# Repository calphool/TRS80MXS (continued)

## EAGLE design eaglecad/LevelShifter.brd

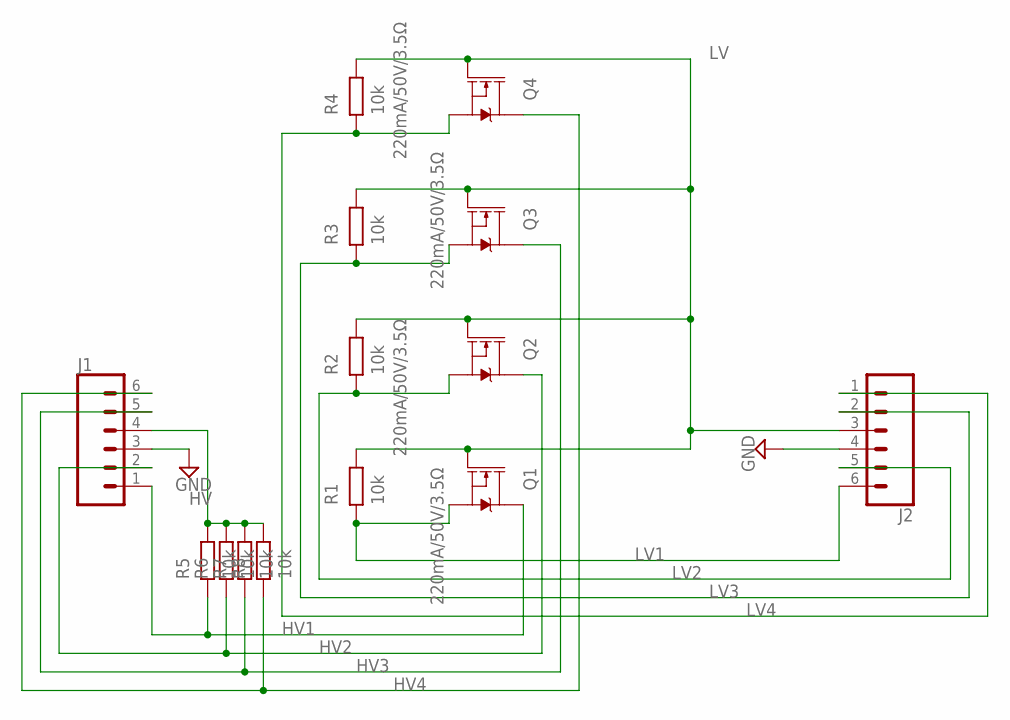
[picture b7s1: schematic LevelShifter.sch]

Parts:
J1, J2: CONN_06NO_SILK_NO_POP; 1X06_NO_SILK
Q1, Q2, Q3, Q4: 220mA/50V/3.5Ω; SOT23-3
R1, R2, R3, R4, R5, R6, R7, R8: 10k; RESC1608X60

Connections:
GND: J1.3, J2.4
HV: J1.4, R5.2, R6.2, R7.2, R8.2
HV1: J1.1, Q1.3 (D), R5.1
HV2: J1.2, Q2.3 (D), R6.1
HV3: J1.5, Q3.3 (D), R7.1
HV4: J1.6, Q4.3 (D), R8.1
LV: J2.3, Q1.1 (G), Q2.1 (G), Q3.1 (G), Q4.1 (G), R1.2, R2.2, R3.2, R4.2
LV1: J2.6, Q1.2 (S), R1.1
LV2: J2.5, Q2.2 (S), R2.1
LV3: J2.2, Q3.2 (S), R3.1
LV4: J2.1, Q4.2 (S), R4.1

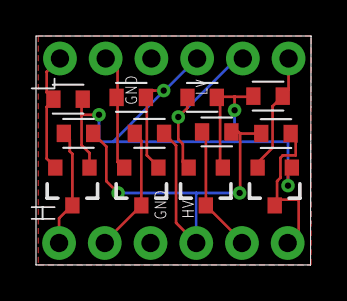
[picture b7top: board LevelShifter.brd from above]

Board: 2 copper layers, 15.3 x 12.7 mm, 14 parts (0 on the bottom side), 11 nets.

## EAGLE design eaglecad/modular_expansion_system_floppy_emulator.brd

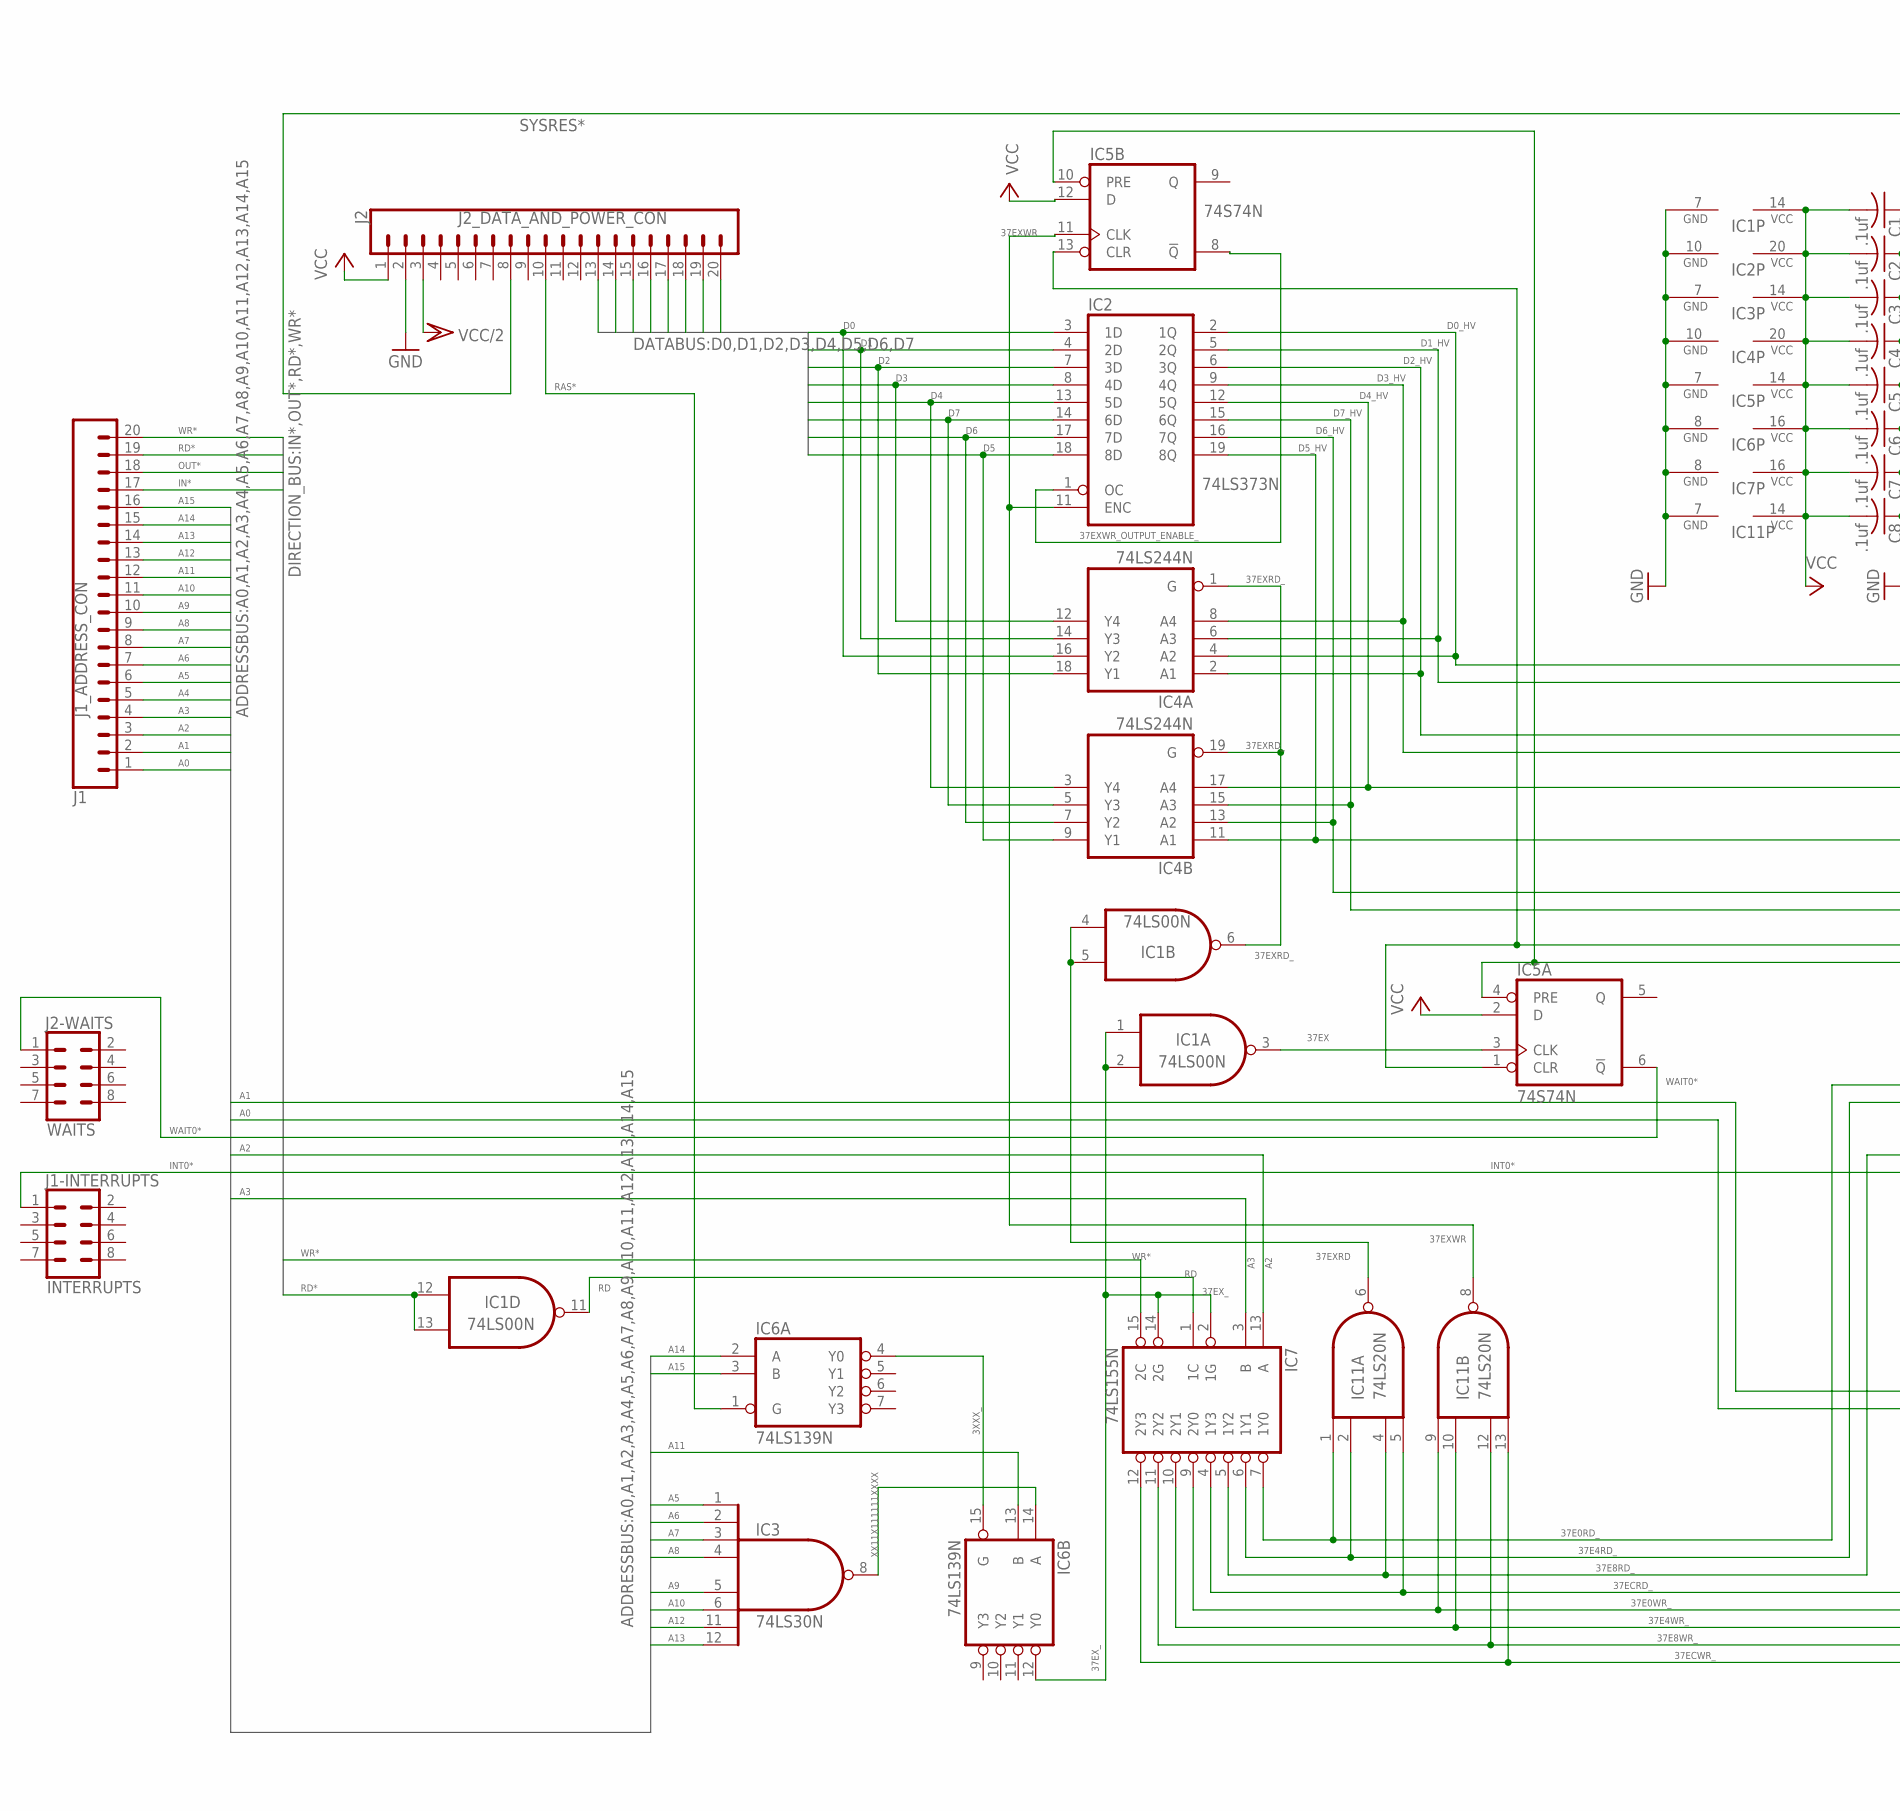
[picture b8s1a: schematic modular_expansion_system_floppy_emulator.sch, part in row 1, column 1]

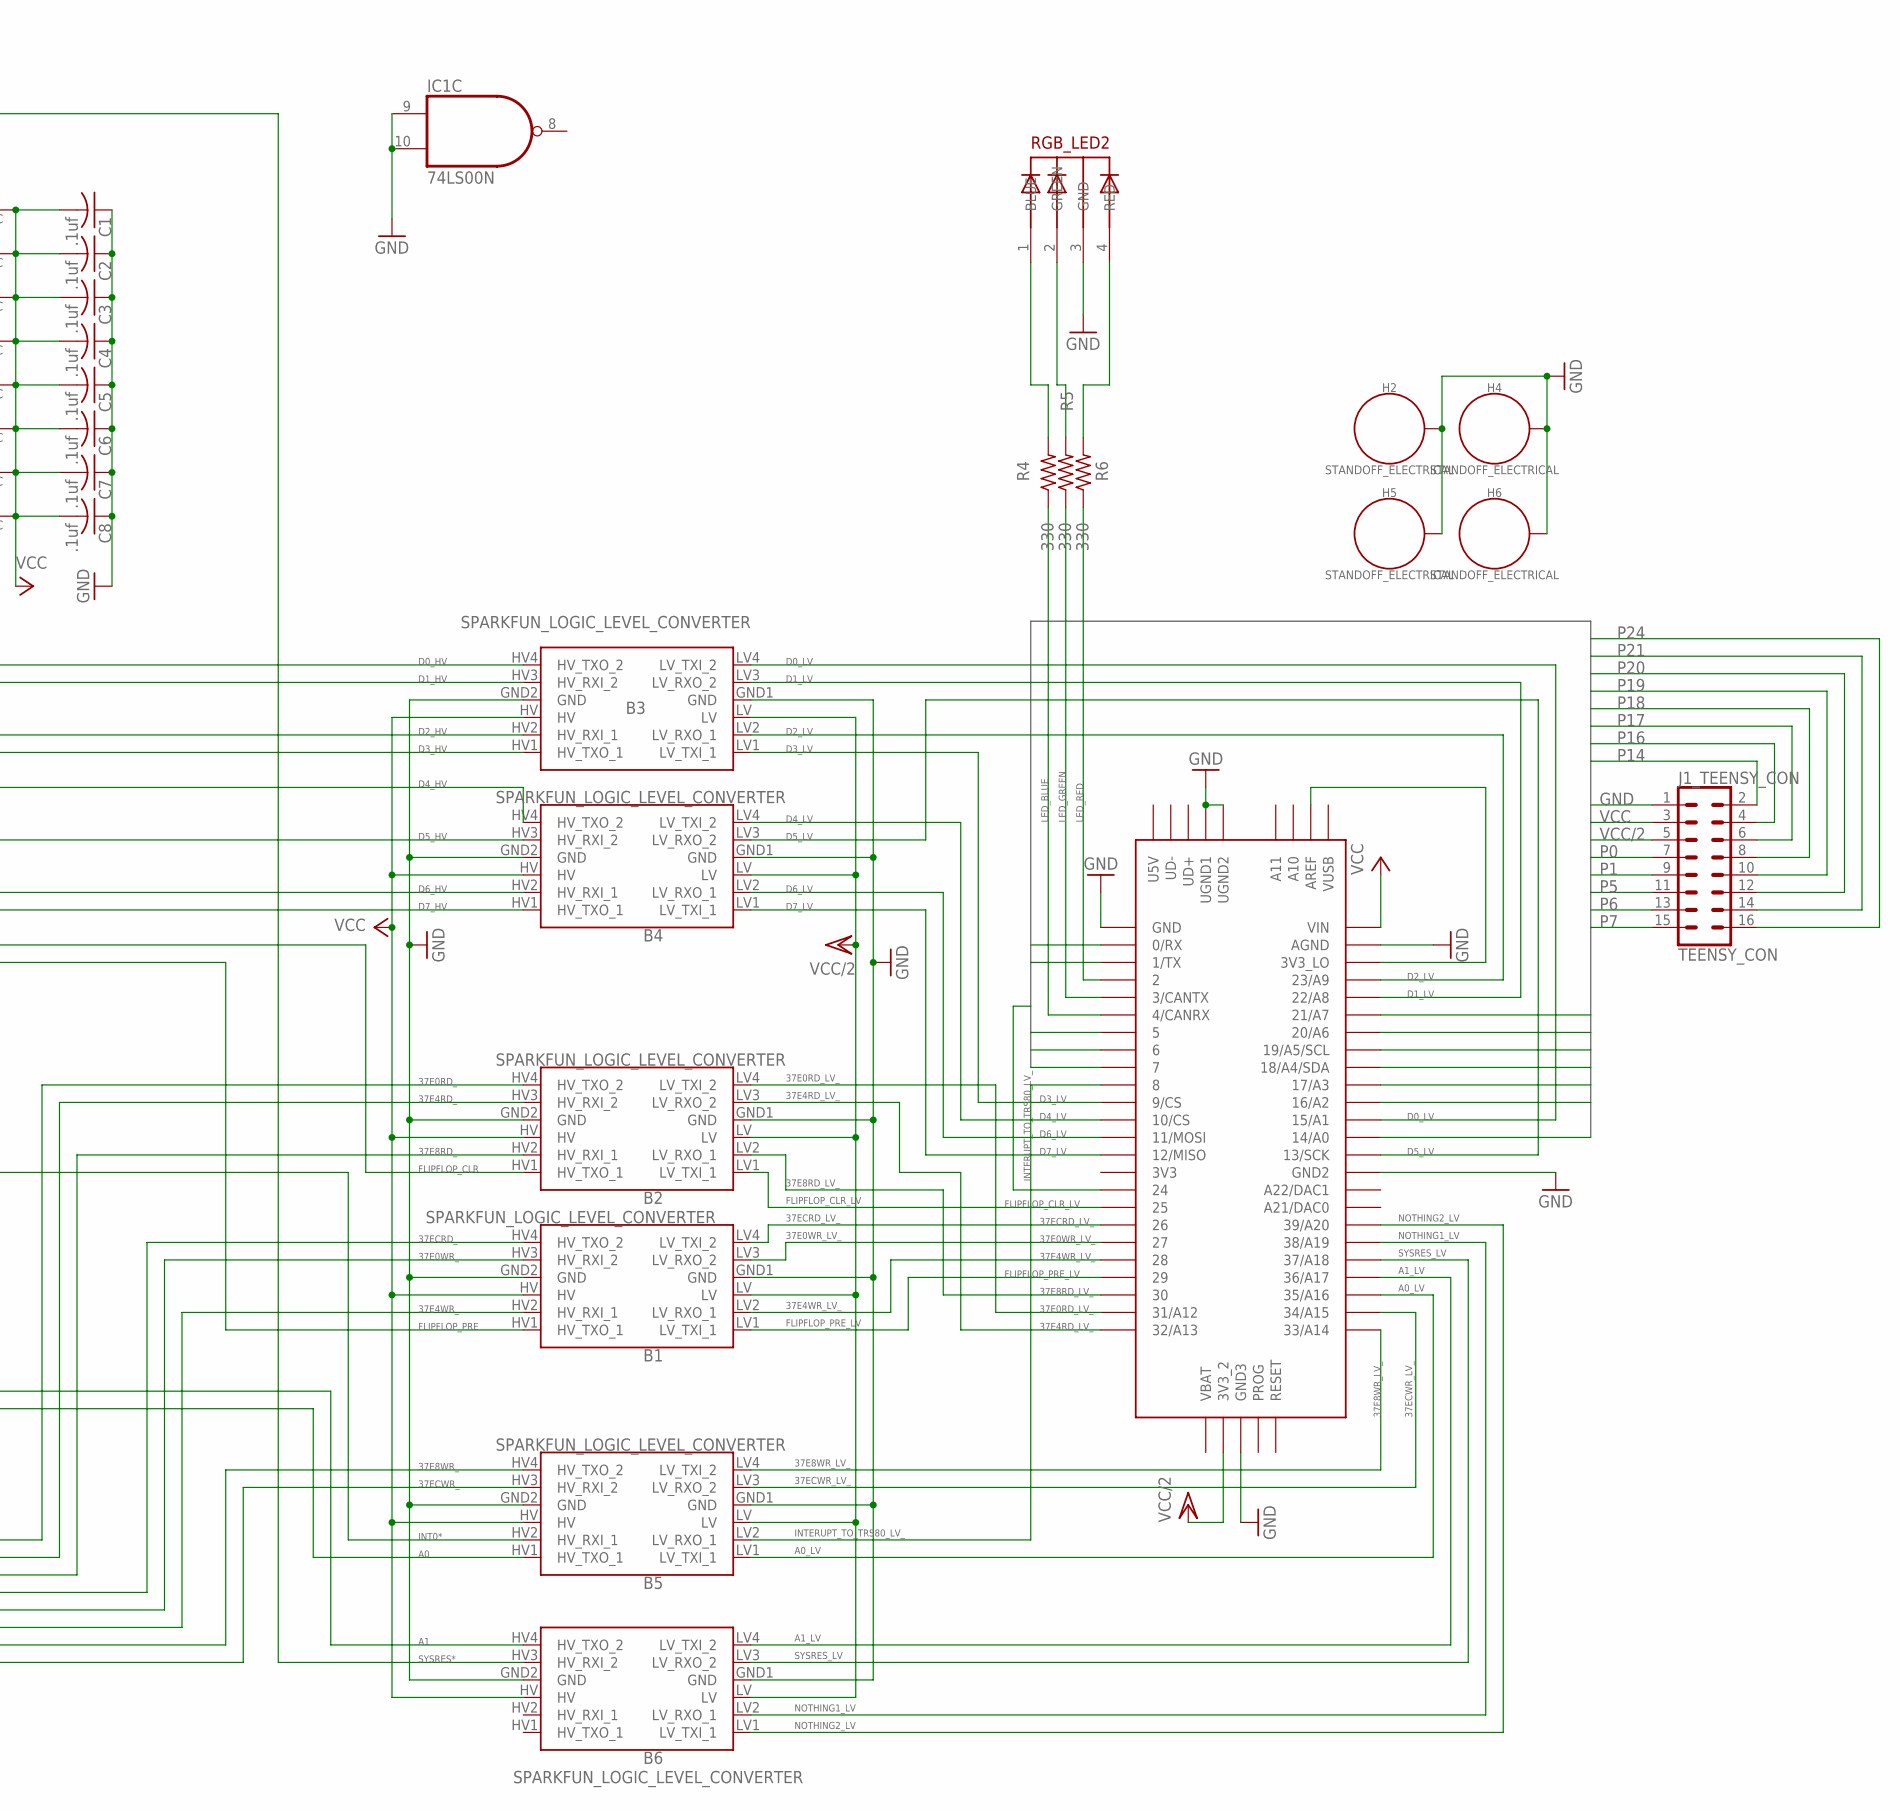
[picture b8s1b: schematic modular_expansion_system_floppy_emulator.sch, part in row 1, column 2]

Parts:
B1, B2, B3, B4, B5, B6: SPARKFUN_LOGIC_LEVEL_CONVERTER
C1, C2, C3, C4, C5, C6, C7, C8: .1uf; C025-024X044
H2, H4, H5, H6: STANDOFF_ELECTRICAL; STANDOFF-ELECTRICAL
IC1: 74LS00N; DIL14
IC2: 74LS373N; DIL20
IC3: 74LS30N; DIL14
IC4: 74LS244N; DIL20
IC5: 74S74N; DIL14
IC6: 74LS139N; DIL16
IC7: 74LS155N; DIL16
IC11: 74LS20N; DIL14
J1-INTERRUPTS: INTERRUPTS; 2X4
J1_ADDRESS_CON: J1; 1X20
J1_TEENSY_CON: TEENSY_CON; 2X8
J2-WAITS: WAITS; 2X4
J2_DATA_AND_POWER_CON: J2; 1X20
R4, R5, R6: 330; 0204V
RGB_LED2: 5MMRGBLED; LED5MMRGB
U$2: TEENSY_3.5/3.6

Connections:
3XXX_: IC6.4 (Y0), IC6.15 (G)
37E0RD_: B2.HV4 (HV_TXO_2), IC7.7 (1Y0), IC11.1 (I0)
37E0RD_LV_: B2.LV4 (LV_TXI_2), U$2.31/A12
37E0WR_: B1.HV3 (HV_RXI_2), IC7.9 (2Y0), IC11.9 (I0)
37E0WR_LV_: B1.LV3 (LV_RXO_2), U$2.27
37E4RD_: B2.HV3 (HV_RXI_2), IC7.6 (1Y1), IC11.2 (I1)
37E4RD_LV_: B2.LV3 (LV_RXO_2), U$2.32/A13
37E4WR_: B1.HV2 (HV_RXI_1), IC7.10 (2Y1), IC11.10 (I1)
37E4WR_LV_: B1.LV2 (LV_RXO_1), U$2.28
37E8RD_: B2.HV2 (HV_RXI_1), IC7.5 (1Y2), IC11.4 (I2)
37E8RD_LV_: B2.LV2 (LV_RXO_1), U$2.30
37E8WR_: B5.HV4 (HV_TXO_2), IC7.11 (2Y2), IC11.12 (I2)
37E8WR_LV_: B5.LV4 (LV_TXI_2), U$2.33/A14
37ECRD_: B1.HV4 (HV_TXO_2), IC7.4 (1Y3), IC11.5 (I3)
37ECRD_LV_: B1.LV4 (LV_TXI_2), U$2.26
37ECWR_: B5.HV3 (HV_RXI_2), IC7.12 (2Y3), IC11.13 (I3)
37ECWR_LV_: B5.LV3 (LV_RXO_2), U$2.34/A15
37EX: IC1.3 (O), IC5.3 (CLK)
37EXRD: IC1.4 (I0), IC1.5 (I1), IC11.6 (O)
37EXRD_: IC1.6 (O), IC4.1 (G), IC4.19 (G)
37EXWR: IC2.11 (ENC), IC5.11 (CLK), IC11.8 (O)
37EXWR_OUTPUT_ENABLE_: IC2.1 (OC), IC5.8 (!Q)
37EX_: IC1.1 (I0), IC1.2 (I1), IC6.12 (Y0), IC7.2 (1G), IC7.14 (2G)
A0: B5.HV1 (HV_TXO_1), J1_ADDRESS_CON.1
A0_LV: B5.LV1 (LV_TXI_1), U$2.35/A16
A1: B6.HV4 (HV_TXO_2), J1_ADDRESS_CON.2
A1_LV: B6.LV4 (LV_TXI_2), U$2.36/A17
A2: IC7.13 (A), J1_ADDRESS_CON.3
A3: IC7.3 (B), J1_ADDRESS_CON.4
A4: J1_ADDRESS_CON.5
A5: IC3.1 (I0), J1_ADDRESS_CON.6
A6: IC3.2 (I1), J1_ADDRESS_CON.7
A7: IC3.3 (I2), J1_ADDRESS_CON.8
A8: IC3.4 (I3), J1_ADDRESS_CON.9
A9: IC3.5 (I4), J1_ADDRESS_CON.10
A10: IC3.6 (I5), J1_ADDRESS_CON.11
A11: IC6.13 (B), J1_ADDRESS_CON.12
A12: IC3.11 (I6), J1_ADDRESS_CON.13
A13: IC3.12 (I7), J1_ADDRESS_CON.14
A14: IC6.2 (A), J1_ADDRESS_CON.15
A15: IC6.3 (B), J1_ADDRESS_CON.16
D0: IC2.3 (1D), IC4.16 (Y2), J2_DATA_AND_POWER_CON.20
D0_HV: B3.HV4 (HV_TXO_2), IC2.2 (1Q), IC4.4 (A2)
D0_LV: B3.LV4 (LV_TXI_2), U$2.15/A1
D1: IC2.4 (2D), IC4.14 (Y3), J2_DATA_AND_POWER_CON.19
D1_HV: B3.HV3 (HV_RXI_2), IC2.5 (2Q), IC4.6 (A3)
D1_LV: B3.LV3 (LV_RXO_2), U$2.22/A8
D2: IC2.7 (3D), IC4.18 (Y1), J2_DATA_AND_POWER_CON.18
D2_HV: B3.HV2 (HV_RXI_1), IC2.6 (3Q), IC4.2 (A1)
D2_LV: B3.LV2 (LV_RXO_1), U$2.23/A9
D3: IC2.8 (4D), IC4.12 (Y4), J2_DATA_AND_POWER_CON.17
D3_HV: B3.HV1 (HV_TXO_1), IC2.9 (4Q), IC4.8 (A4)
D3_LV: B3.LV1 (LV_TXI_1), U$2.9/CS
D4: IC2.13 (5D), IC4.3 (Y4), J2_DATA_AND_POWER_CON.16
D4_HV: B4.HV4 (HV_TXO_2), IC2.12 (5Q), IC4.17 (A4)
D4_LV: B4.LV4 (LV_TXI_2), U$2.10/CS
D5: IC2.18 (8D), IC4.9 (Y1), J2_DATA_AND_POWER_CON.15
D5_HV: B4.HV3 (HV_RXI_2), IC2.19 (8Q), IC4.11 (A1)
D5_LV: B4.LV3 (LV_RXO_2), U$2.13/SCK
D6: IC2.17 (7D), IC4.7 (Y2), J2_DATA_AND_POWER_CON.14
D6_HV: B4.HV2 (HV_RXI_1), IC2.16 (7Q), IC4.13 (A2)
D6_LV: B4.LV2 (LV_RXO_1), U$2.11/MOSI
D7: IC2.14 (6D), IC4.5 (Y3), J2_DATA_AND_POWER_CON.13
D7_HV: B4.HV1 (HV_TXO_1), IC2.15 (6Q), IC4.15 (A3)
D7_LV: B4.LV1 (LV_TXI_1), U$2.12/MISO
FLIPFLOP_CLR: B2.HV1 (HV_TXO_1), IC5.1 (CLR), IC5.13 (CLR)
FLIPFLOP_CLR_LV: B2.LV1 (LV_TXI_1), U$2.25
FLIPFLOP_PRE: B1.HV1 (HV_TXO_1), IC5.4 (PRE), IC5.10 (PRE)
FLIPFLOP_PRE_LV: B1.LV1 (LV_TXI_1), U$2.29
GND: B1.GND1 (GND), B1.GND2 (GND), B2.GND1 (GND), B2.GND2 (GND), B3.GND1 (GND), B3.GND2 (GND), B4.GND1 (GND), B4.GND2 (GND), B5.GND1 (GND), B5.GND2 (GND), B6.GND1 (GND), B6.GND2 (GND), C1.1, C2.1, C3.1, C4.1, C5.1, C6.1, C7.1, C8.1, H2.P1, H4.P1, H5.P1, H6.P1, IC1.7 (GND), IC1.9 (I0), IC1.10 (I1), IC2.10 (GND), IC3.7 (GND), IC4.10 (GND), IC5.7 (GND), IC6.8 (GND), IC7.8 (GND), IC11.7 (GND), J1_TEENSY_CON.1, J2_DATA_AND_POWER_CON.2, RGB_LED2.3 (GND), U$2.AGND, U$2.GND, U$2.GND2, U$2.GND3, U$2.UGND1, U$2.UGND2
IN*: J1_ADDRESS_CON.17
INT0*: B5.HV2 (HV_RXI_1), J1-INTERRUPTS.1
INTERUPT_TO_TRS80_LV_: B5.LV2 (LV_RXO_1), U$2.8
LED_BLUE: R4.1, U$2.4/CANRX
LED_GREEN: R5.1, U$2.3/CANTX
LED_RED: R6.1, U$2.2
unnamed: U$2.3V3_LO, U$2.AREF
unnamed: R5.2, RGB_LED2.2 (GREEN)
unnamed: R4.2, RGB_LED2.1 (BLUE)
unnamed: R6.2, RGB_LED2.4 (RED)
NOTHING1_LV: B6.LV2 (LV_RXO_1), U$2.38/A19
NOTHING2_LV: B6.LV1 (LV_TXI_1), U$2.39/A20
OUT*: J1_ADDRESS_CON.18
P0: J1_TEENSY_CON.7, U$2.0/RX
P1: J1_TEENSY_CON.9, U$2.1/TX
P5: J1_TEENSY_CON.11, U$2.5
P6: J1_TEENSY_CON.13, U$2.6
P7: J1_TEENSY_CON.15, U$2.7
P14: J1_TEENSY_CON.2, U$2.14/A0
P16: J1_TEENSY_CON.4, U$2.16/A2
P17: J1_TEENSY_CON.6, U$2.17/A3
P18: J1_TEENSY_CON.8, U$2.18/A4/SDA
P19: J1_TEENSY_CON.10, U$2.19/A5/SCL
P20: J1_TEENSY_CON.12, U$2.20/A6
P21: J1_TEENSY_CON.14, U$2.21/A7
P24: J1_TEENSY_CON.16, U$2.24
RAS*: IC6.1 (G), J2_DATA_AND_POWER_CON.10
RD: IC1.11 (O), IC7.1 (1C)
RD*: IC1.12 (I0), IC1.13 (I1), J1_ADDRESS_CON.19
SYSRES*: B6.HV3 (HV_RXI_2), J2_DATA_AND_POWER_CON.8
SYSRES_LV: B6.LV3 (LV_RXO_2), U$2.37/A18
VCC: B1.HV, B2.HV, B3.HV, B4.HV, B5.HV, B6.HV, C1.2, C2.2, C3.2, C4.2, C5.2, C6.2, C7.2, C8.2, IC1.14 (VCC), IC2.20 (VCC), IC3.14 (VCC), IC4.20 (VCC), IC5.2 (D), IC5.12 (D), IC5.14 (VCC), IC6.16 (VCC), IC7.16 (VCC), IC11.14 (VCC), J1_TEENSY_CON.3, J2_DATA_AND_POWER_CON.1, U$2.VIN
VCC/2: B1.LV, B2.LV, B3.LV, B4.LV, B5.LV, B6.LV, J1_TEENSY_CON.5, J2_DATA_AND_POWER_CON.3, U$2.3V3_2
WAIT0*: IC5.6 (!Q), J2-WAITS.1
WR*: IC7.15 (2C), J1_ADDRESS_CON.20
XX11X111111XXXX: IC3.8 (O), IC6.14 (A)

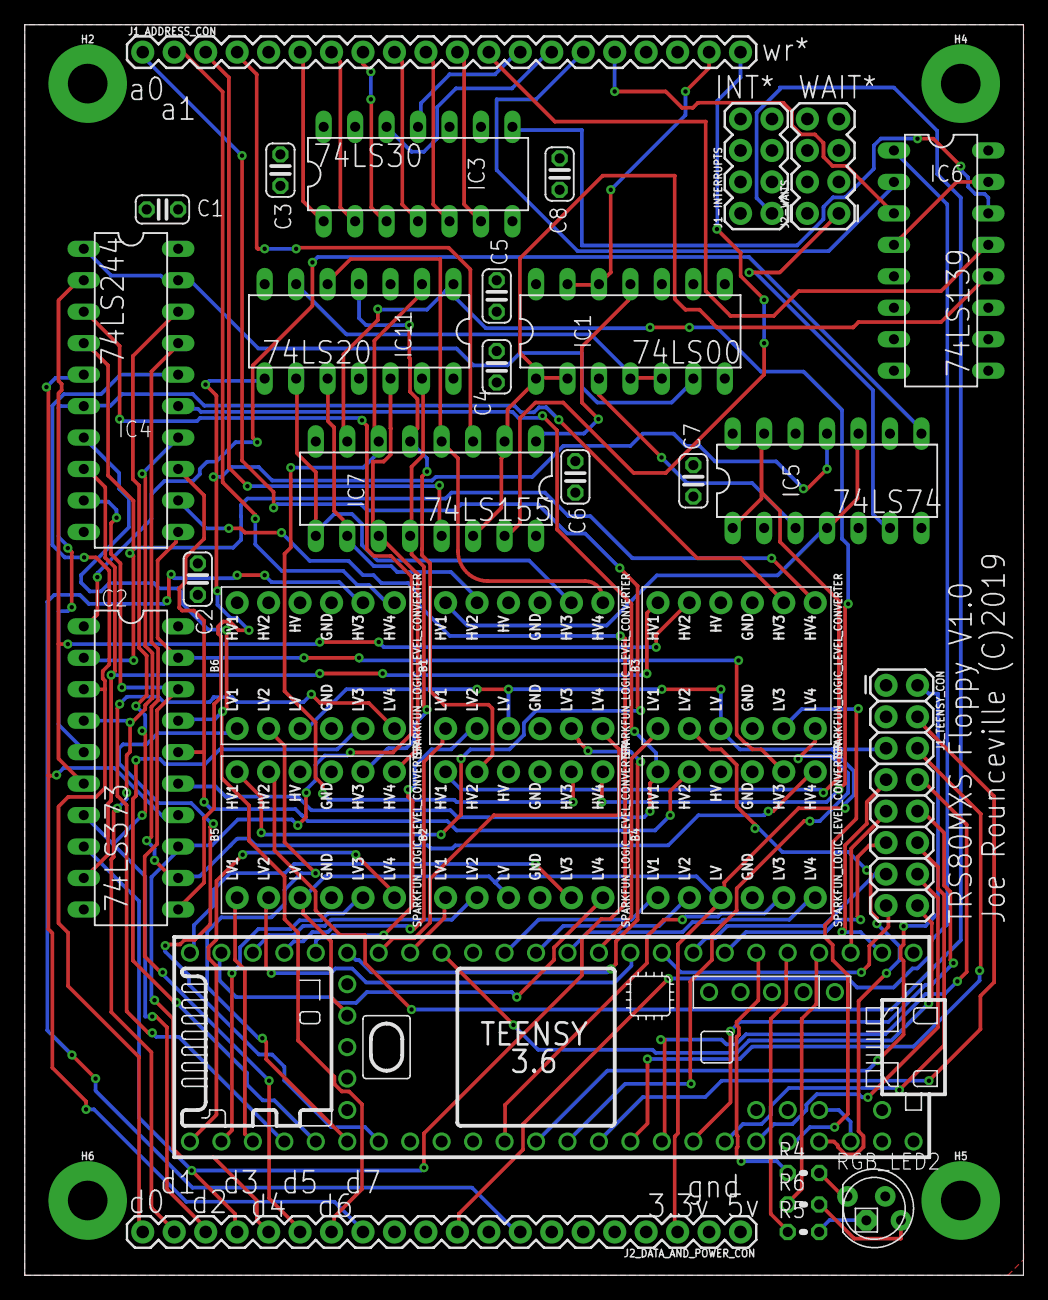
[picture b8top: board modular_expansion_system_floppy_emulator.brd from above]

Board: 2 copper layers, 80.6 x 101.0 mm, 36 parts (0 on the bottom side), 103 nets.

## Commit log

2019-02-04 all three boards designed
2019-02-04 small change to game board
2019-02-04 cleaned up wire stub
2019-02-04 added PDFs and libaries
2019-02-04 moved traces away from crystal module
2019-02-04 added gitignore
2019-02-07 added text to boards
2019-02-08 removed soft reset for vdp, added 12 voice sound
2019-02-10 tweaked sound circuit
2019-02-11 boards as they were when sent to allpcb
2019-02-22 updated sound board, fixed mirrored headers
2019-03-02 bug in the base board RD, WR, IN, and OUT signals
2019-03-03 fix for screwed up base board signals
2019-03-17 drive emulation code
2019-03-17 tweaks for new board design
2019-03-17 readme update
2019-03-19 change comments in PLD code
2019-04-13 updated readme and minor updates to schematic for gs board
2019-04-22 added inductor to grfx brd and removed extra 7805
2019-05-04 added switching supply to base pcb
2019-05-23 updated pic
2019-05-23 readme updat
2019-05-23 update pic
2019-05-27 added sound code
2019-05-31 added video link to audio demo
2019-06-16 fixed WRITE code in drive emulation and added music stuff
2019-06-16 small tweaks for music stuff
2019-06-28 implemented TRS80MXS command line utility
2019-06-28 updated schematics, boards, and pdfs
2019-06-28 added bill of materials
2019-07-04 added WIFI board design - untested
2019-07-05 updated esp32 board
2019-07-26 added power supply stuff
2019-07-26 fix readme
2019-09-08 first 'working' ESP32 code and board design
2019-10-22 small README update and some tweaks for the esp32 module
2020-01-01 changed readme
2020-01-02 renamed trs80mxs.c to mxs.c
2020-02-12 readme update and mixer board design
2020-05-04 added pacman game
2020-05-09 updated pacman clone game
2020-05-09 update to pacman clone code
2020-05-09 updated pacman game
2020-05-09 fixed westward going pacman sprite
2020-05-10 tweaks to pacman code
2020-05-15 pacman code updates
2020-05-15 pacman tweaks
2020-05-16 pacman updates
2020-05-16 added ghost eye movement behaviors to pacman
2020-05-16 pacman tweaks - level counter
2020-05-18 implemented pacman fruit behavior
2020-05-18 boot screen changes for pacman
2020-05-19 tweaked graphics card to match older TRS80 joysticks and tweaked pacman game
2020-05-19 switched ghost sprite priority in pacman to better handle TMS9918 hardware bug
2020-05-23 cleaned up pacman code a bit
2020-06-07 joystick pin fixes to match old alphastick
2020-06-09 added splash screen for TRS80MXS
2020-06-29 updated graphics board to make joysticks compatible with old games
2020-09-22 Fixes for mount, stand alond joystick boards, level shifters Adafruit
2020-09-22 changed orientation of fuse and switch on power supply board
2020-09-22 updated power supply pdf
2020-09-22 printed circuit board for power supply pdf
2021-01-24 various fixes
